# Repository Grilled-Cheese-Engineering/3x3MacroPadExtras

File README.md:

# **3x3 Macro Pad Extras**

Documentation written by JStudios6118

This repository contains the KiCad design files and files for 3D printing the case of the board as well as an assembly guide to build your own.

## **Firmware**

Download the firmware from our master ZMK Firmware Repository: [GCE ZMK Firmware](https://github.com/Grilled-Cheese-Engineering/GCE_ZMK_Firmware_Downloads)

## **KiCad Files**

### Project Files

All of the KiCad files are provided in the the KiCad directory. [KiCad Files](/KiCad/)

Some of the symbols used may not be present. Make sure you have Seeed Studios' XIAO Kicad Symbol Library and ScottoKeebs Kicad Library. 

### Production Files

You can find the JLCPCB production ready files in this directory as well. Just download the zip files in the directory and upload to JLCPCB (or any other fabrication service) to order. [Production Files](/KiCad/production/)

## **3D Printing**

To 3D print the case, use the provided 3MF files in the 3D Printing directory. [3D Printing](/3DPrinting/)

# Bill of Materials

### **Equipment**

- Soldering Iron
- Solder
- SMD Soldering Equipment (read note)
    - The Microncontroller Unit is the only surface mount component in this build. While it likely can be hand soldered with a regular soldering iron, the battery pads are inaccesible to a soldering iron.

### **Required Parts**
- (x1) Macro Board PCB
- (x1) Seeed Studio XIAO nRF52840
- (x9) 1N4148 IN4148 Diode DO-35
- (x9) Standard MX Keyboard Switches
- (x1) EC11 Rotary Encoder (With pushbutton)

### **Optional Parts**
- (x1) 1k Ohm Through Hole Resistor
- (x1) 3mm Led (Any color)
- (x1) Lipo Battery* (Any capacity)

*In our testing, a 600mah battery lasts about 7-9 days using bluetooth.

# Build Instructions

Building the macro pad is very straightforward as long as you do things in the right order.

## **1. Solder the MCU to the Board**

Solder the Seeed Studio XIAO board to the pads on the top-left corner of the pcb. The USB-C port should be facing outwards. It is recommended to use an SMD soldering technique such as reflow soldering for this step so the battery pads can be soldered but hand soldering also works at the expense of not having a battery.

> **WARNING:** If soldering the battery pads to the PCB, use less solder paste than you think. It is very easy to bridge the pads and if that happens you will have to desolder the MCU. Trust me, I've had that happen everytime I build one.

## **2. Check the Solder Joints**

Use a multimeter to check for continuity between pins. It is important that there is no bridging between any of the pads. Here is a picture from the schematic showing what pads connect to what parts of the PCB: [Wiring Diagram](images/macropad_wiring_schematic.png). If ANY pads are bridged you will need to fix them. There should not be continuity between the battery positive and negative holes on the board.

## **3. (Optional) Solder the Power LED**

Solder an LED of your choice to the site marked LED. The square pad should be connected to the anode of the LED. Also solder preferably a 1k Ohm Resistor into the site marked R1. Plug in the board to power and the LED should light up. Make sure to snip the leads after doing so.

## **4. Solder the Diodes**

Next solder the diodes to the board. It is recommended to solder them to the front face of the board. Use the reference on the back of the board to get the correct polarity. Snip the leads close to the board once finished.

## **5. Solder the Mechanical Switches**

Now solder the MX Keyswitches onto the front face of the board. If the switch does not have stabilizers built in, it will be challenging to keep the switches straight. The keyplate piece of the 3D printed files can help keep the switches aligned if that is the case.

## **6. Add the Rotary Encoder**

Finally solder the EC11 Rotary Encoder to the PCB on to the front face. It is recommended to solder the mounting pins first to help hold the rotary encoder in place while soldering the other pins.

## **7. (Optional) Solder the Battery**

Solder the your battery to the site marked J1. Be sure that the battery is connected with the correct polarity and the pins are not bridged. The battery was not soldered previously in the guide to protect it from heat from the soldering iron.

## **8. Flash the Firmware**

Flash the firmware to the MCU. If this is the first firmware to be flashed to the device, it should pop up in your file manager automatically. If not, double press the small reset button on the MCU. Finally, drag and drop the uf2 file to the device. It will automatically disconnect and reboot. It may give an error when you drop it onto the device but that is normal.

> You can download the firmware in the Releases Section of this repository: [Firmware Downloads](https://github.com/Grilled-Cheese-Engineering/GCE_ZMK_Firmware_Downloads)

# **Congratulations! You just built the 3x3 Macropad!**

You can use ZMK Studio to customize the keybindings. Please raise an issue if you have any problems with this guide.

-Grilled Cheese Engineering

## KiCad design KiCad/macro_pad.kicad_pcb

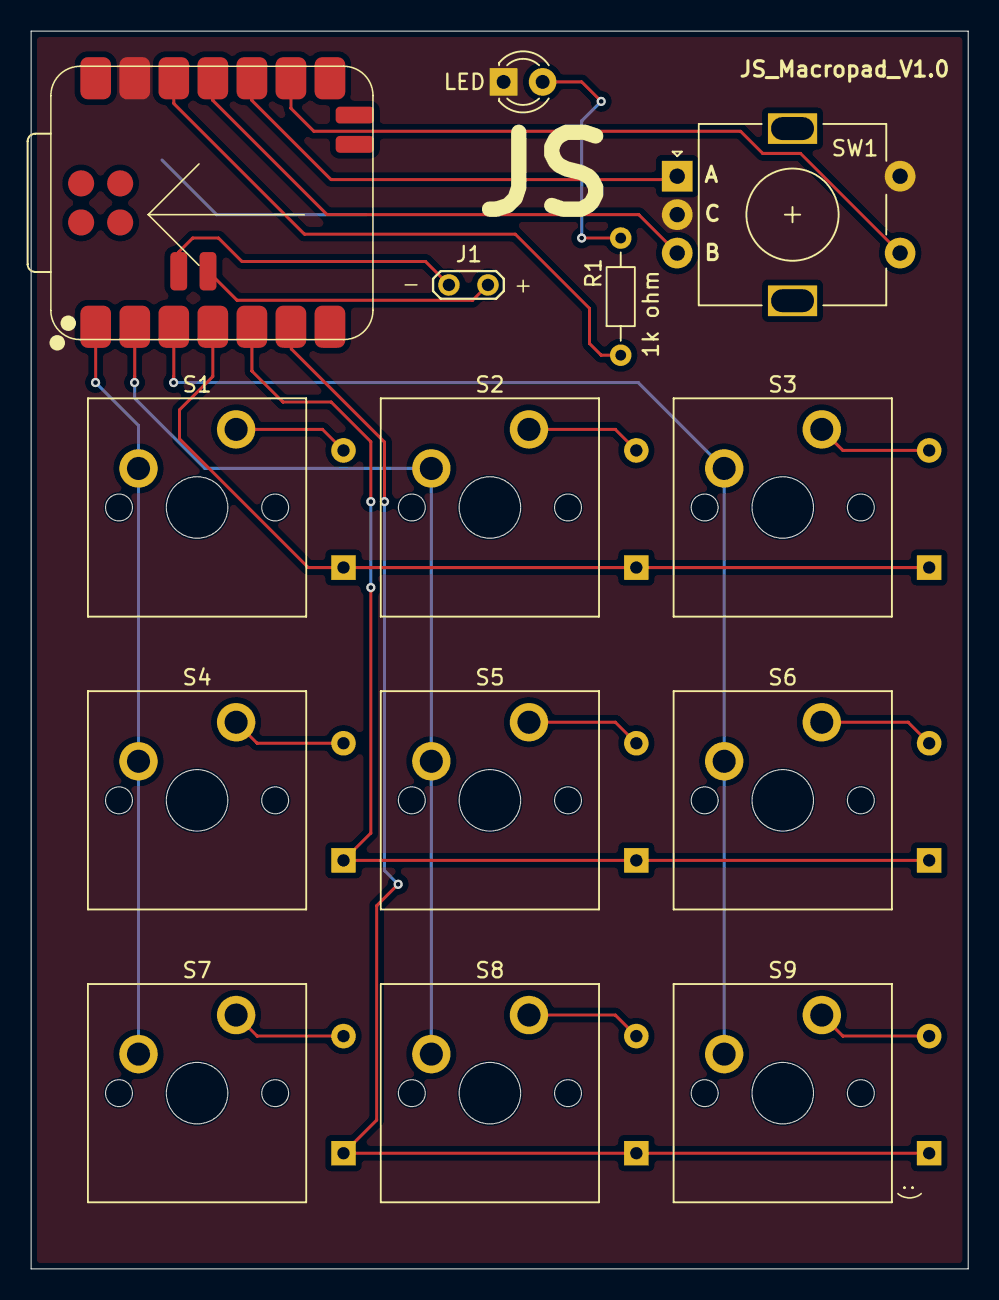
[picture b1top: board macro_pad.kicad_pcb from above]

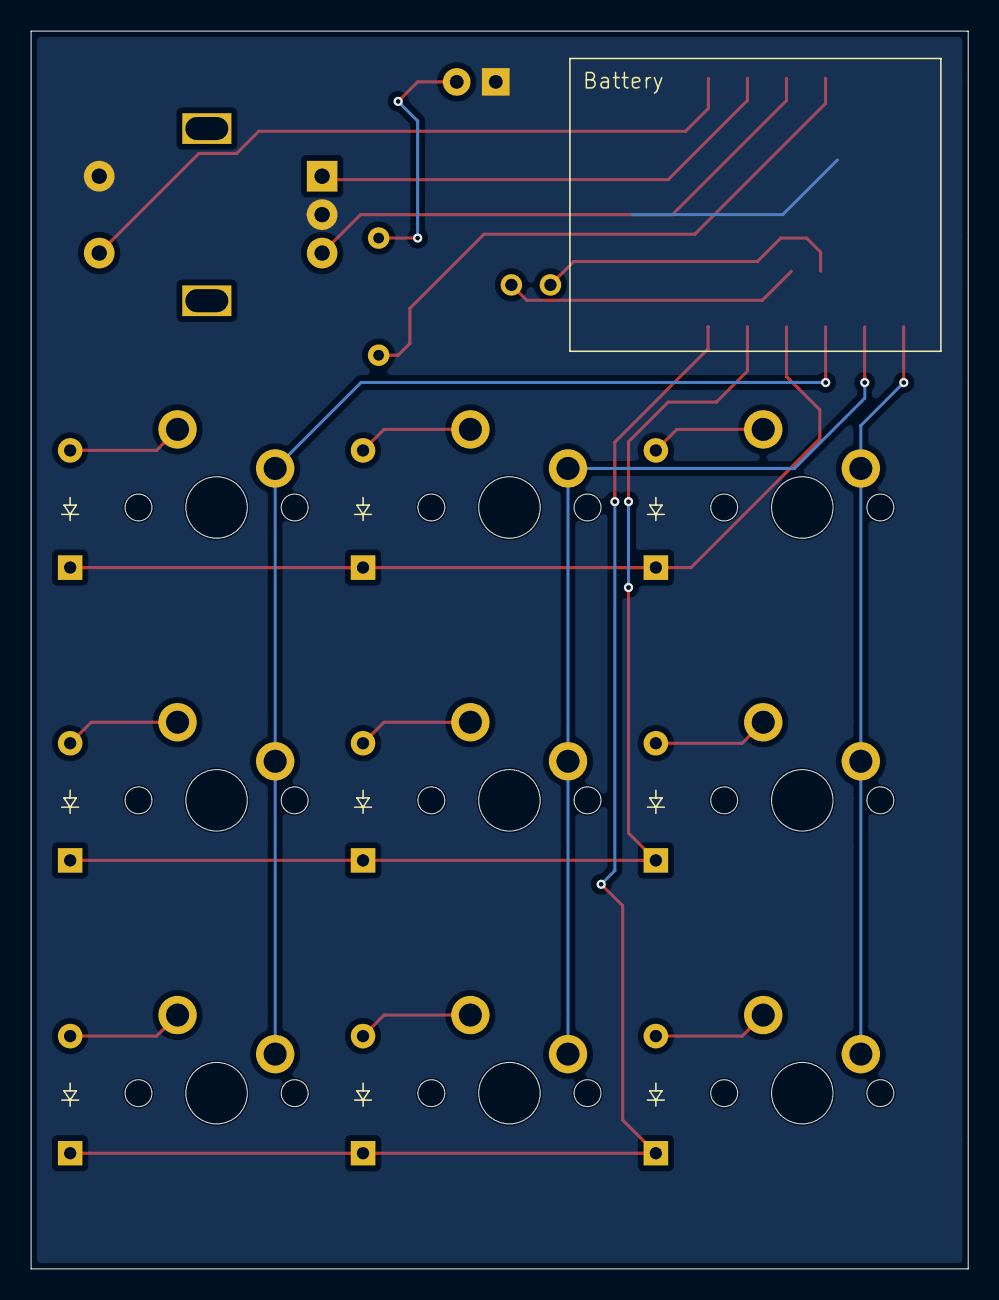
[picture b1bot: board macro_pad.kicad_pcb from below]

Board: 2 copper layers, 61.0 x 80.5 mm, 23 parts (9 on the bottom side), 23 nets.

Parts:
D1, D2, D3, D4, D5, D6, D7, D8, D9: Diode_DO-35
J1: Conn_01x02; TestPoint_2Pads_Pitch2.54mm_Drill0.8mm
LED: LED; LED_D3.0mm
R1: R; R_Axial_DIN0204_L3.6mm_D1.6mm_P7.62mm_Horizontal
S1, S2, S3, S4, S5, S6, S7, S8, S9: MX_PCB_1.00u
SW1: RotaryEncoder; RotaryEncoder_Alps_EC11E-Switch_Vertical_H20mm
U1: XIAO-nRF52840-SMD

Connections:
+3.3V: R1.1, U1.12 (3V3_OUT)
Column 0: S1.1, S4.1, S7.1, U1.1 (D0)
Column 1: S2.1, S5.1, S8.1, U1.2 (D1)
Column 2: S3.1, S6.1, S9.1, U1.3 (D2)
GND: LED.1 (K), SW1.C, SW1.S2, U1.13 (GND)
unnamed: D1.2 (A), S1.2
unnamed: D2.2 (A), S2.2
unnamed: D3.2 (A), S3.2
unnamed: D4.2 (A), S4.2
unnamed: D5.2 (A), S5.2
unnamed: D6.2 (A), S6.2
unnamed: D7.2 (A), S7.2
unnamed: D8.2 (A), S8.2
unnamed: D9.2 (A), S9.2
unnamed: LED.2 (A), R1.2
unnamed: J1.1, U1.20 (GND)
unnamed: J1.2, U1.19 (VBAT)
Rotary 1A: SW1.A, U1.10 (D9)
Rotary 1B: SW1.B, U1.11 (D10)
Rotary Button: SW1.S1, U1.9 (D8)
Row 0: D1.1 (K), D2.1 (K), D3.1 (K), U1.4 (D3)
Row 1: D4.1 (K), D5.1 (K), D6.1 (K), U1.5 (D4)
Row 2: D7.1 (K), D8.1 (K), D9.1 (K), U1.6 (D5)

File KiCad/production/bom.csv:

Designator,Footprint,Quantity,Value,LCSC Part #
"D1, D2, D3, D4, D5, D6, D7, D8, D9",Diode_DO-35,9,~,
J1,TestPoint_2Pads_Pitch2.54mm_Drill0.8mm,1,Conn_01x02,
LED,LED_D3.0mm,1,LED,
R1,R_Axial_DIN0204_L3.6mm_D1.6mm_P7.62mm_Horizontal,1,R,
"S1, S2, S3, S4, S5, S6, S7, S8, S9",MX_PCB_1.00u,9,~,
SW1,RotaryEncoder_Alps_EC11E-Switch_Vertical_H20mm,1,RotaryEncoder,
U1,XIAO-nRF52840-SMD,1,XIAO-nRF52840-SMD,
